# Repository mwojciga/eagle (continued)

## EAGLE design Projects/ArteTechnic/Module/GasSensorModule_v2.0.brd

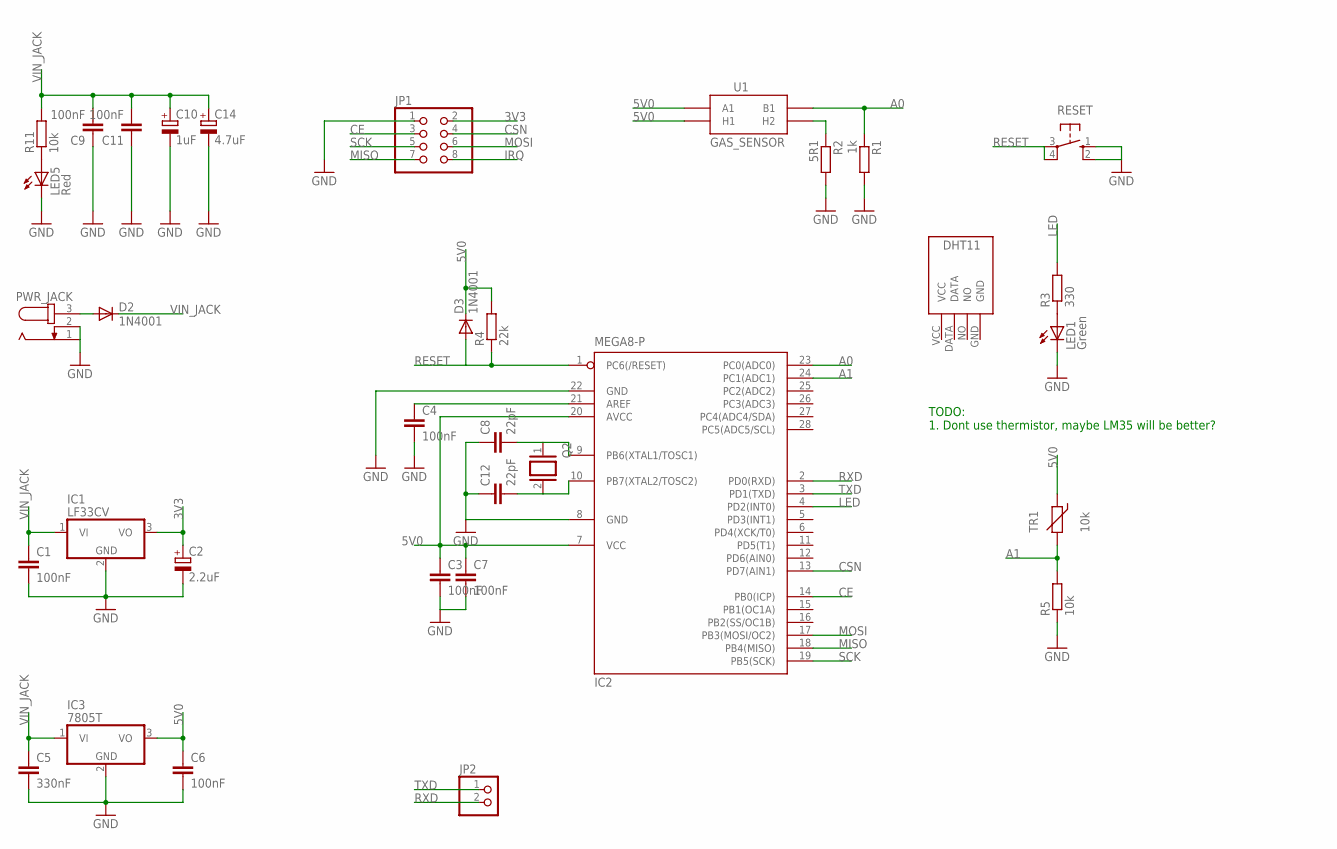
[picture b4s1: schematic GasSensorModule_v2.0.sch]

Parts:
C1, C3, C4, C6, C7, C9, C11: 100nF; C025-025X050
C2: 2.2uF; E2,5-5
C5: 330nF; C025-025X050
C8, C12: 22pF; C025-025X050
C10: 1uF; E2,5-5
C14: 4.7uF; E2,5-5
D2, D3: 1N4001; DO41-10
IC1: LF33CV; TO220H
IC2: MEGA8-P; DIL28-3
IC3: 7805T; TO220H
JP1: PINHD-2X4; 2X04
JP2: PINHD-1X2/90; 1X02/90
LED1: Green; LED3MM
LED5: Red; LED3MM
PWR_JACK: JACK-PLUG0; SPC4077
Q2: XTAL/S; QS
R1: 1k; 0207/10
R2: 5R1; 0207/10
R3: 330; 0207/10
R4: 22k; 0207/10
R5, R11: 10k; 0207/10
RESET: 10-XX; B3F-10XX
TR1: 10k; RS-2,5
U1: GAS_SENSOR; MQ-3
U$1: DHT11-PION.

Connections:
3V3: C2.+, IC1.3 (VO), JP1.2
5V0: C3.1, C6.1, C7.1, D3.C, IC2.7 (VCC), IC2.20 (AVCC), IC3.3 (VO), R4.2, TR1.1, U1.A1, U1.HA (H1)
A0: IC2.23 (PC0(ADC0)), R1.1, U1.B1
A1: IC2.24 (PC1(ADC1)), R5.2, TR1.2
CE: IC2.14 (PB0(ICP)), JP1.3
CSN: IC2.13 (PD7(AIN1)), JP1.4
GND: C1.2, C2.-, C3.2, C4.2, C5.2, C6.2, C7.2, C8.1, C9.1, C10.-, C11.1, C12.1, C14.-, IC1.2 (GND), IC2.8 (GND), IC2.22 (GND), IC3.2 (GND), JP1.1, LED1.K (C), LED5.K (C), PWR_JACK.1, PWR_JACK.2, R1.2, R2.2, R5.1, RESET.1 (S), RESET.2 (S1)
IRQ: JP1.8
LED: IC2.4 (PD2(INT0)), R3.2
MISO: IC2.18 (PB4(MISO)), JP1.7
MOSI: IC2.17 (PB3(MOSI/OC2)), JP1.6
unnamed: C4.1, IC2.21 (AREF)
unnamed: R2.1, U1.HB (H2)
unnamed: D2.A, PWR_JACK.3
unnamed: LED1.A, R3.1
unnamed: LED5.A, R11.1
unnamed: C8.2, IC2.9 (PB6(XTAL1/TOSC1)), Q2.1
unnamed: C12.2, IC2.10 (PB7(XTAL2/TOSC2)), Q2.2
RESET: D3.A, IC2.1 (PC6(/RESET)), R4.1, RESET.3, RESET.4 (P1)
RXD: IC2.2 (PD0(RXD)), JP2.2
SCK: IC2.19 (PB5(SCK)), JP1.5
TXD: IC2.3 (PD1(TXD)), JP2.1
VIN_JACK: C1.1, C5.1, C9.2, C10.+, C11.2, C14.+, D2.C, IC1.1 (VI), IC3.1 (VI), R11.2

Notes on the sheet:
TODO: 1. Dont use thermistor, maybe LM35 will be better?

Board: 2 copper layers, 34 parts (0 on the bottom side), 22 nets, no tracks yet.

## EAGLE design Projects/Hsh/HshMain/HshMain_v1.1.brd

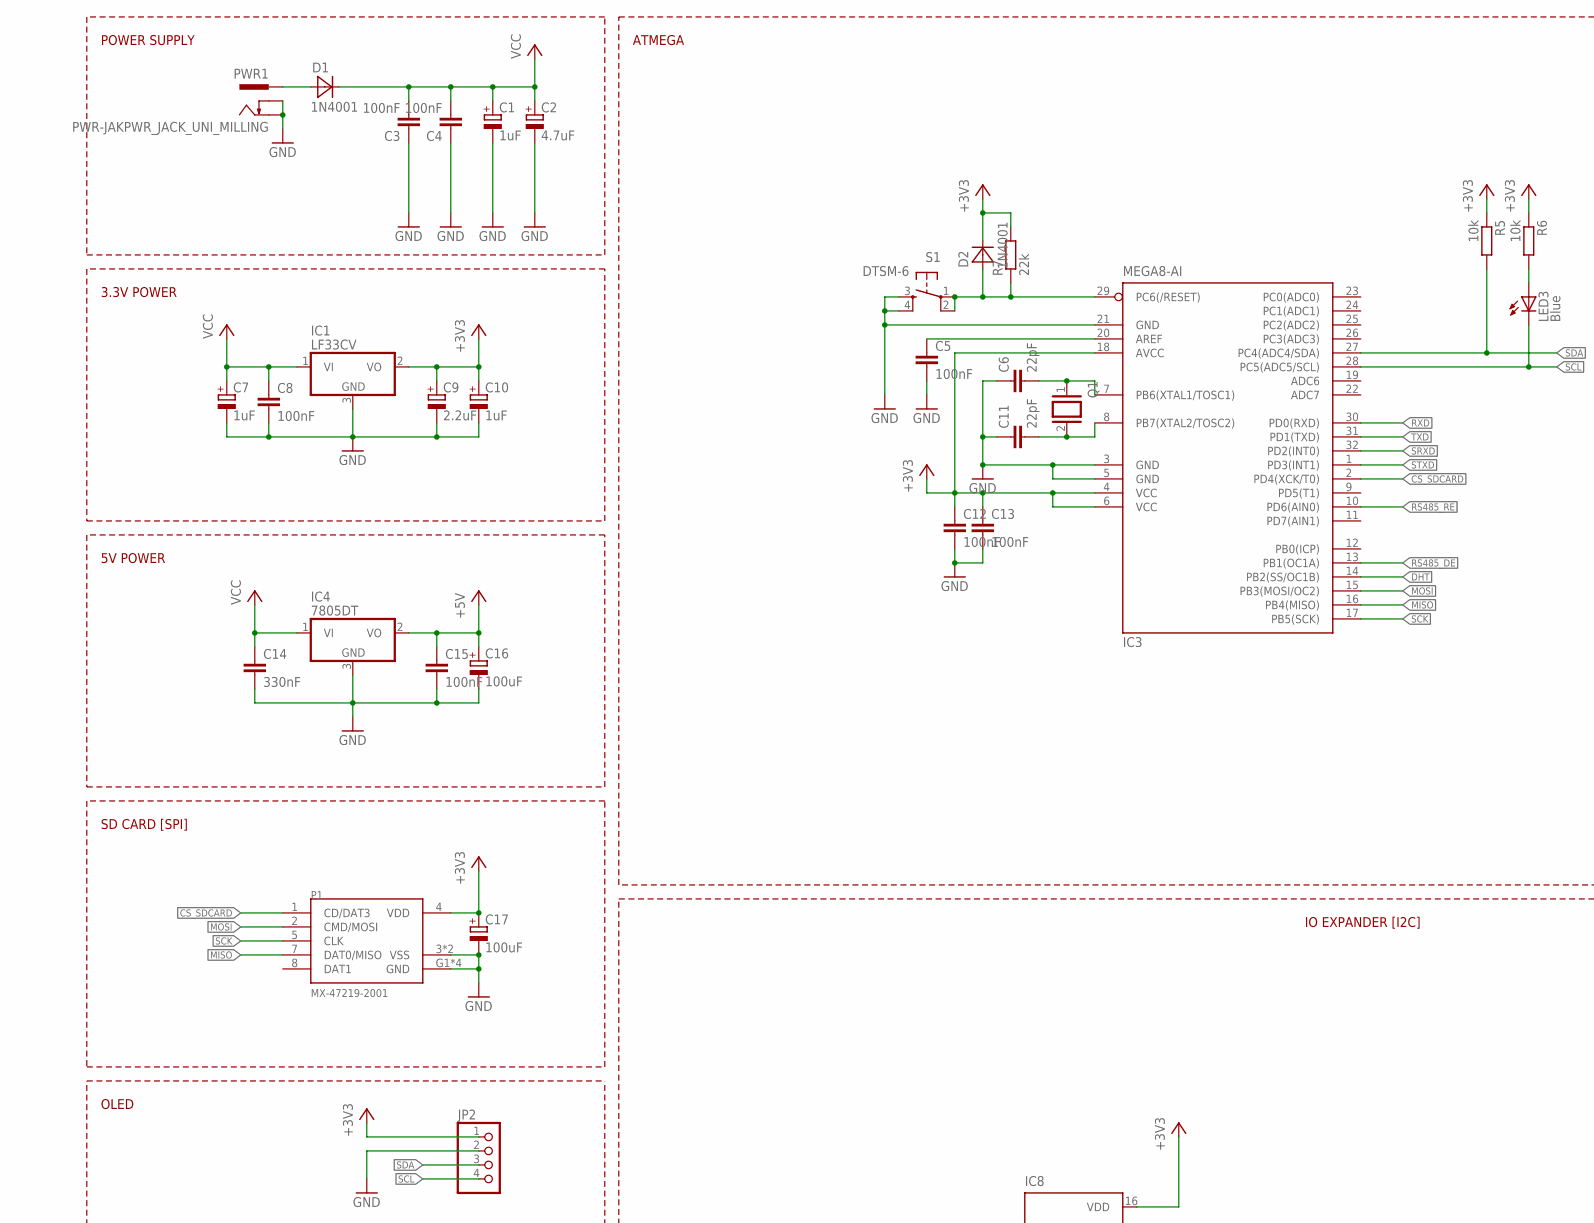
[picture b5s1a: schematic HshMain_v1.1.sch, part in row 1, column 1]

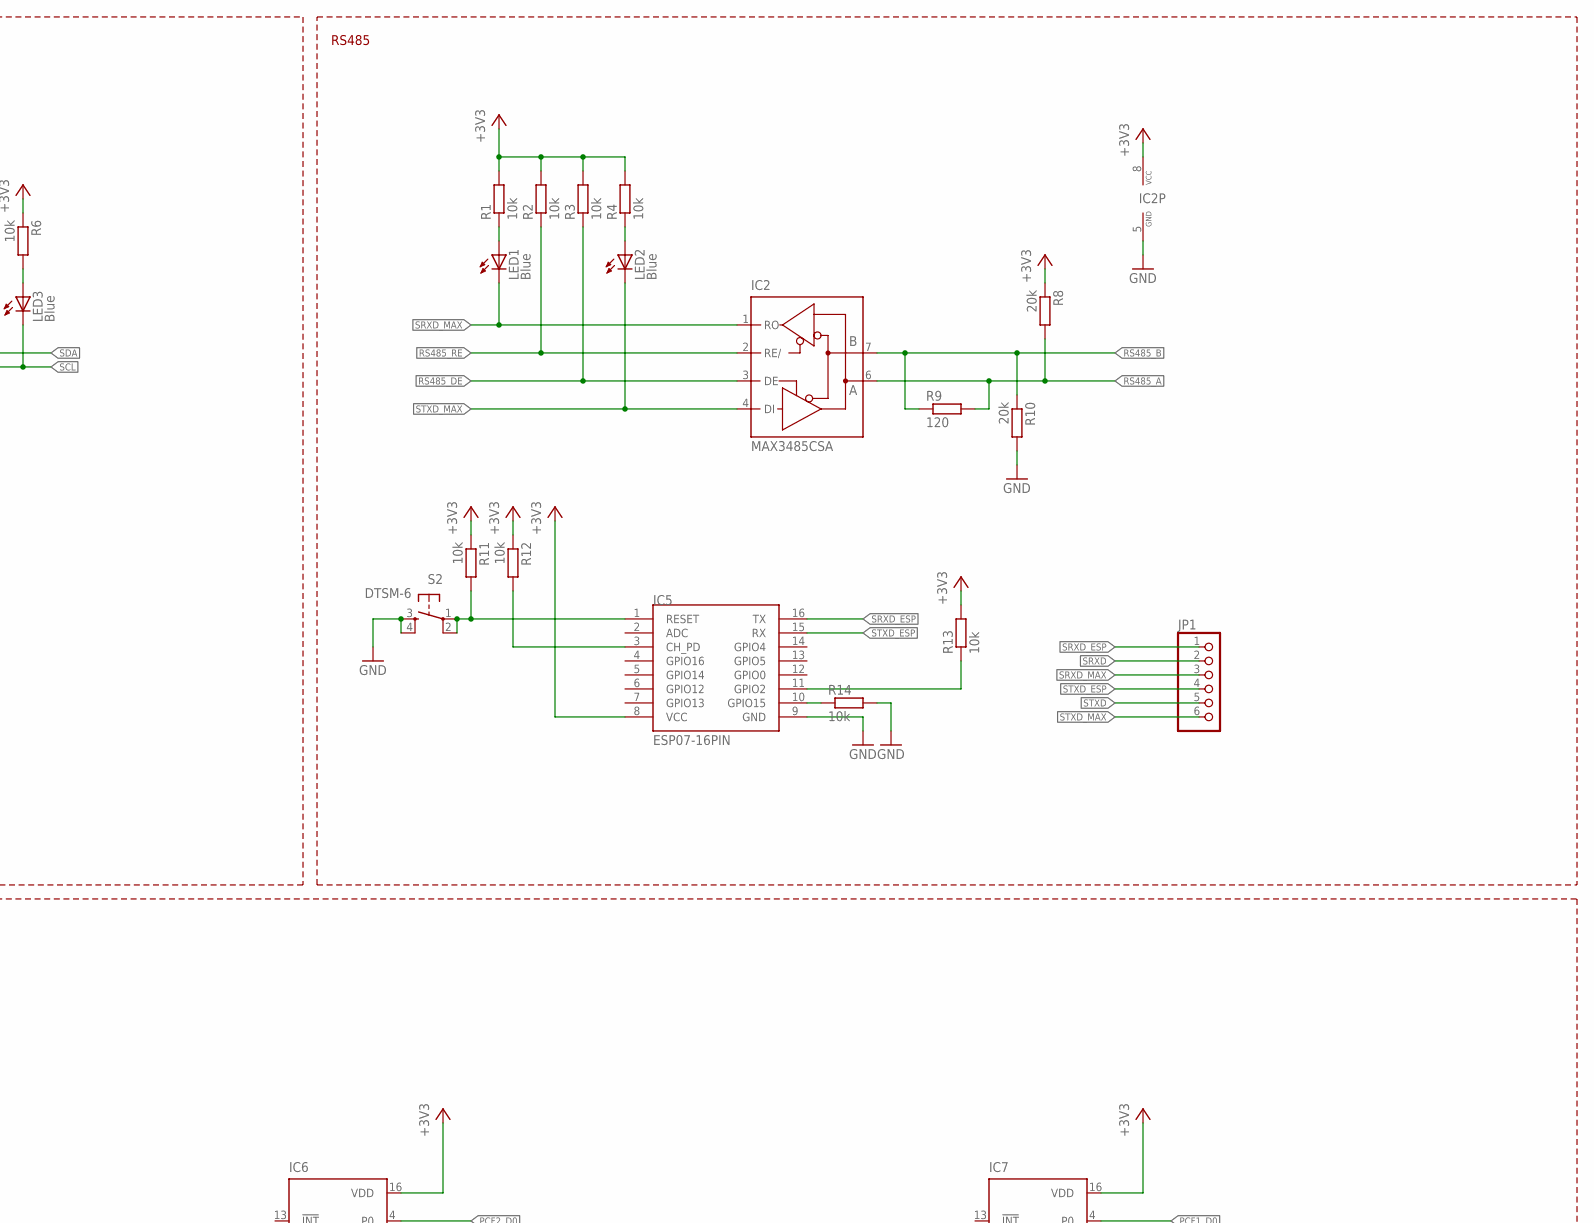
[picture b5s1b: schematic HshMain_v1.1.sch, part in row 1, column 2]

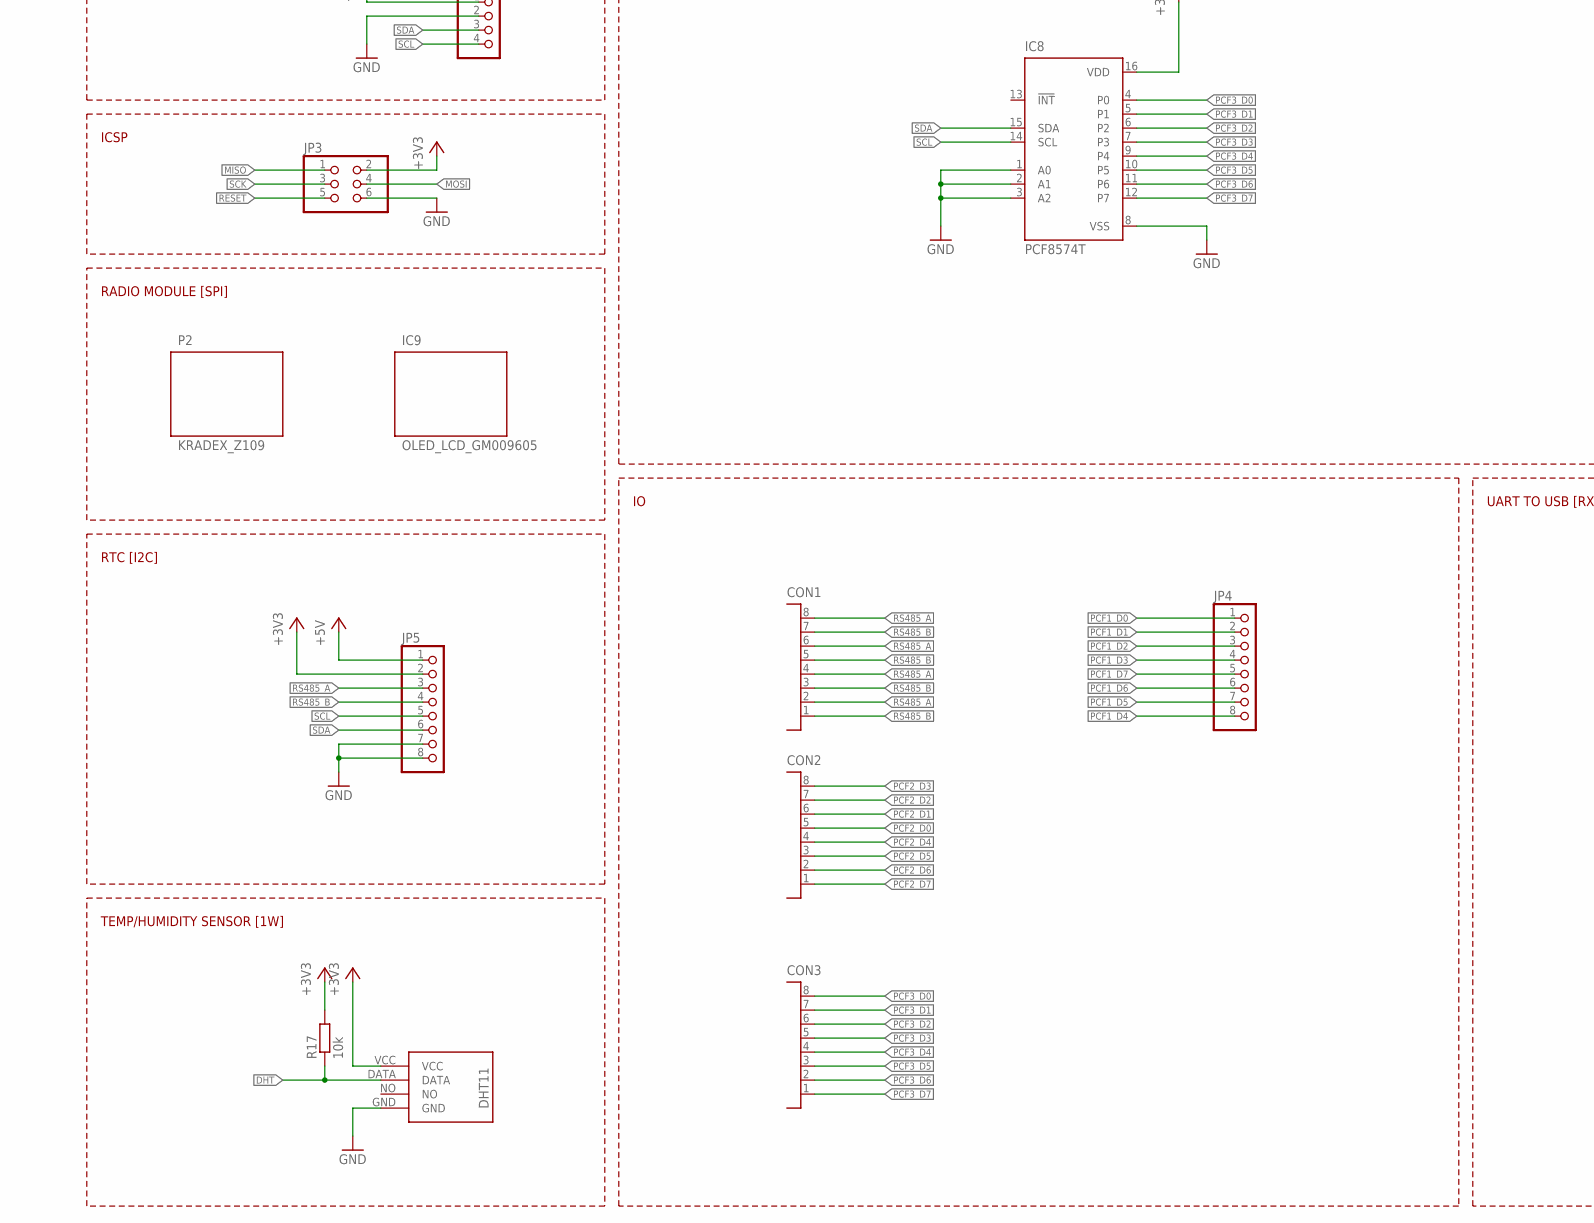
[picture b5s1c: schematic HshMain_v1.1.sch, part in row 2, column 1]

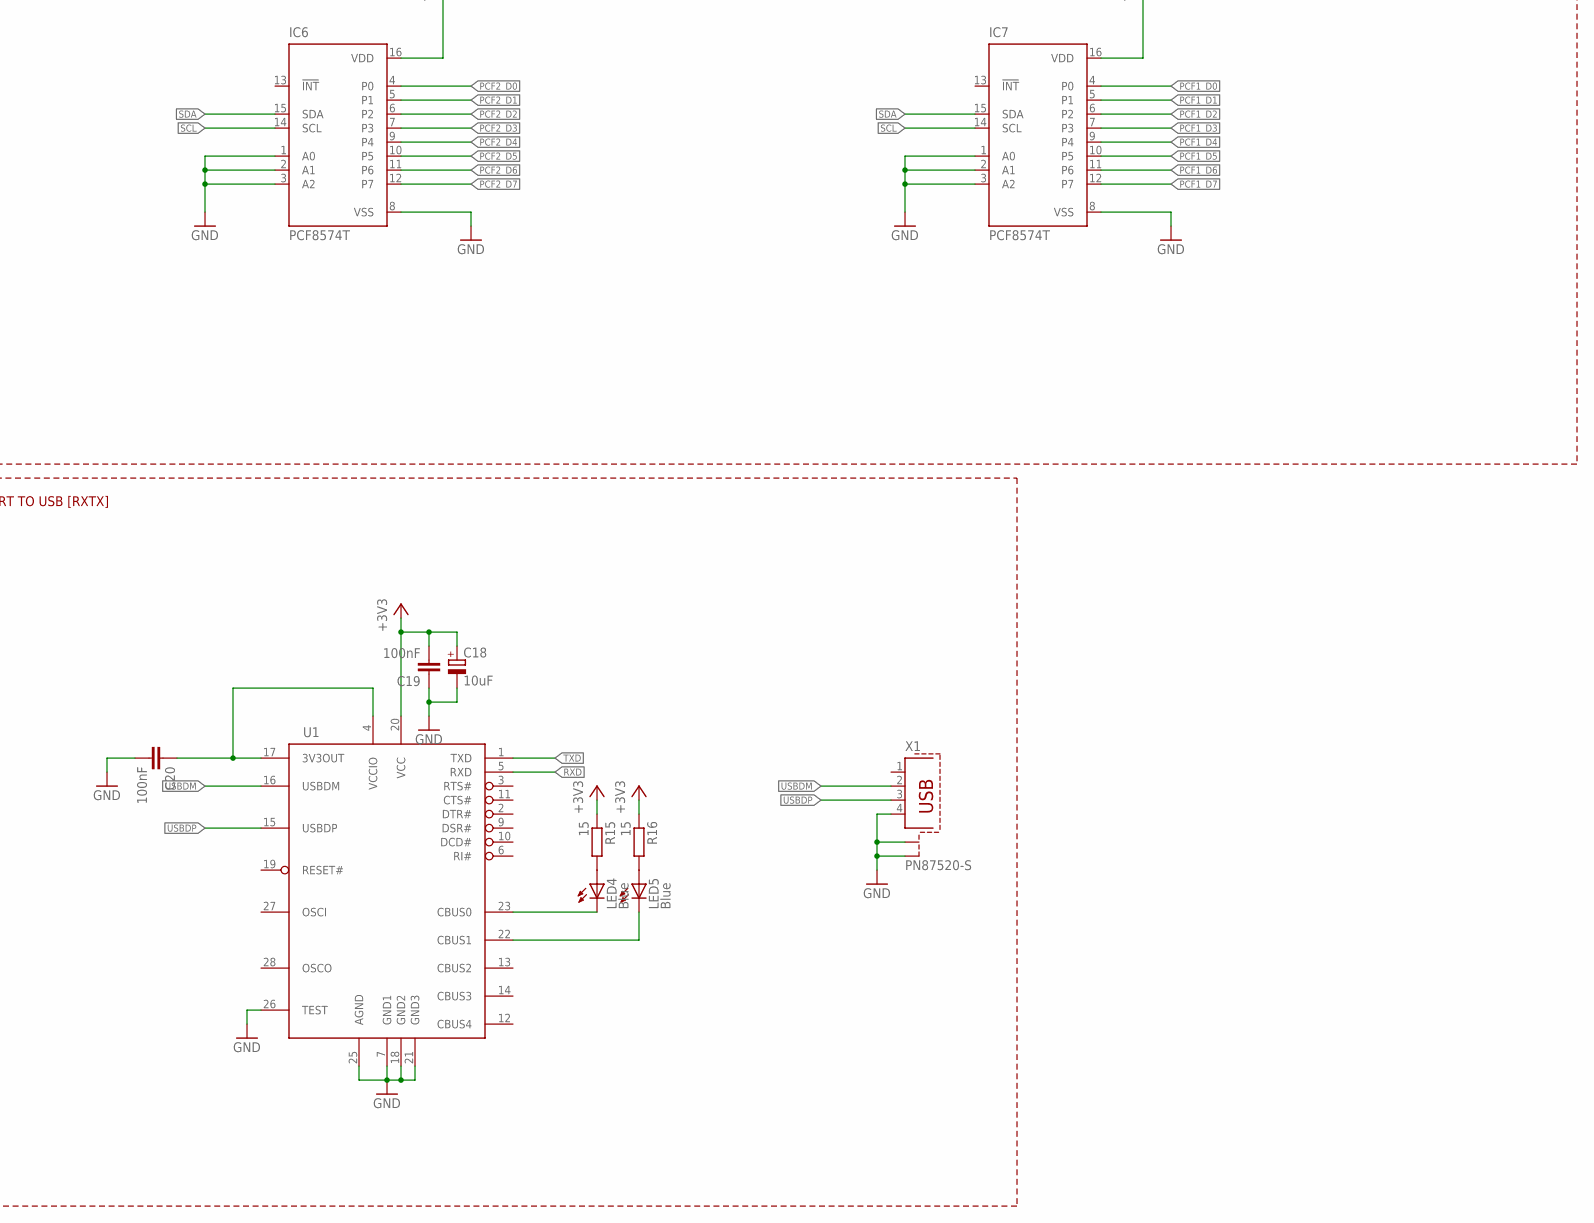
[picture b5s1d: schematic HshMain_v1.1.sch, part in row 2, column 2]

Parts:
C1, C7, C10: 1uF; PANASONIC_B
C2: 4.7uF; PANASONIC_B
C3, C4, C5, C8, C12, C13, C15, C19, C20: 100nF; C0805
C6, C11: 22pF; C0805
C9: 2.2uF; PANASONIC_B
C14: 330nF; C0805
C16, C17: 100uF; PANASONIC_D
C18: 10uF; PANASONIC_B
CON1, CON2, CON3: 15EDGRC-3.81-8P
D1, D2: 1N4001; SMA
IC1: LF33CV; TO252
IC2: MAX3485CSA; SO08
IC3: MEGA8-AI; TQFP32-08
IC4: 7805DT; TO252
IC5: ESP07-16PIN
IC6, IC7, IC8: PCF8574T; SO16W
IC9: OLED_LCD_GM009605
IC10: DHT11-PION.
JP1: PINHD-1X6; 1X06
JP2: PINHD-1X4; 1X04
JP3: PINHD-2X3; 2X03
JP4: PINHD-1X8; 1X08
JP5: PINHD-1X8/90; 1X08/90
LED1, LED2, LED3, LED4, LED5: Blue; SML0805
P1: MX-47219-2001
P2: KRADEX_Z109
PWR1: PWR-JAKPWR_JACK_UNI_MILLING; PWR_JACK_UNI_MILLING
Q1: XTAL/S; QS
R1, R2, R3, R4, R5, R6, R11, R12, R13, R14, R17: 10k; R0805
R7: 22k; R0805
R8, R10: 20k; R0805
R9: 120; R0805
R15, R16: 15; R0805
S1, S2: DTSM-6
U1: FT232RL; SSOP28DB
X1: PN87520-S

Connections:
+3V3: C9.+, C10.+, C12.1, C13.1, C17.+, C18.+, C19.2, D2.C, IC1.2 (VO), IC2.8 (VCC), IC3.4 (VCC), IC3.6 (VCC), IC3.18 (AVCC), IC5.8 (VCC), IC6.16 (VDD), IC7.16 (VDD), IC8.16 (VDD), IC10.VCC, JP2.1, JP3.2, JP5.2, P1.4 (VDD), R1.2, R2.2, R3.2, R4.2, R5.1, R6.1, R7.2, R8.1, R11.1, R12.1, R13.2, R15.1, R16.1, R17.2, U1.20 (VCC)
+5V: C15.1, C16.+, IC4.2 (VO), JP5.1
CS_SDCARD: IC3.2 (PD4(XCK/T0)), P1.1 (CD/DAT3)
DHT: IC3.14 (PB2(SS/OC1B)), IC10.DATA, R17.1
GND: C1.-, C2.-, C3.1, C4.1, C5.2, C6.1, C7.-, C8.2, C9.-, C10.-, C11.1, C12.2, C13.2, C14.2, C15.2, C16.-, C17.-, C18.-, C19.1, C20.2, IC1.3 (GND), IC2.5 (GND), IC3.3 (GND), IC3.5 (GND), IC3.21 (GND), IC4.3 (GND), IC5.9 (GND), IC6.1 (A0), IC6.2 (A1), IC6.3 (A2), IC6.8 (VSS), IC7.1 (A0), IC7.2 (A1), IC7.3 (A2), IC7.8 (VSS), IC8.1 (A0), IC8.2 (A1), IC8.3 (A2), IC8.8 (VSS), IC10.GND, JP2.2, JP3.6, JP5.7, JP5.8, P1.3 (VSS), P1.6 (VSS), P1.G1 (GND), P1.G2 (GND), P1.G3 (GND), P1.G4 (GND), PWR1.-, PWR1.-1 (-), PWR1.-2 (-), PWR1.-3 (-), PWR1.-4 (-), PWR1.-5 (-), PWR1.-6 (-), PWR1.-7 (-), PWR1.-8 (-), PWR1.--, PWR1.--1 (--), PWR1.--2 (--), PWR1.--3 (--), PWR1.--4 (--), PWR1.--5 (--), PWR1.--6 (--), PWR1.--7 (--), PWR1.--8 (--), R10.2, R14.2, S1.3, S1.4, S2.3, S2.4, U1.7 (GND1), U1.18 (GND2), U1.21 (GND3), U1.25 (AGND), U1.26 (TEST), X1.4, X1.S1, X1.S2
MISO: IC3.16 (PB4(MISO)), JP3.1, P1.7 (DAT0/MISO)
MOSI: IC3.15 (PB3(MOSI/OC2)), JP3.4, P1.2 (CMD/MOSI)
unnamed: C5.1, IC3.20 (AREF)
unnamed: LED1.A, R1.1
unnamed: LED2.A, R4.1
unnamed: D1.A, PWR1.+, PWR1.+1 (+), PWR1.+2 (+), PWR1.+3 (+), PWR1.+4 (+), PWR1.+5 (+), PWR1.+6 (+), PWR1.+7 (+), PWR1.+8 (+)
unnamed: LED3.A, R6.2
unnamed: IC5.10 (GPIO15), R14.1
unnamed: IC5.11 (GPIO2), R13.1
unnamed: IC5.1 (RESET), R11.2, S2.1, S2.2
unnamed: IC5.3 (CH_PD), R12.2
unnamed: LED4.C, U1.23 (CBUS0)
unnamed: LED5.C, U1.22 (CBUS1)
unnamed: C6.2, IC3.7 (PB6(XTAL1/TOSC1)), Q1.1
unnamed: LED4.A, R15.2
unnamed: LED5.A, R16.2
unnamed: C11.2, IC3.8 (PB7(XTAL2/TOSC2)), Q1.2
unnamed: C20.1, U1.4 (VCCIO), U1.17 (3V3OUT)
PCF1_D0: IC7.4 (P0), JP4.1
PCF1_D1: IC7.5 (P1), JP4.2
PCF1_D2: IC7.6 (P2), JP4.3
PCF1_D3: IC7.7 (P3), JP4.4
PCF1_D4: IC7.9 (P4), JP4.8
PCF1_D5: IC7.10 (P5), JP4.7
PCF1_D6: IC7.11 (P6), JP4.6
PCF1_D7: IC7.12 (P7), JP4.5
PCF2_D0: CON2.5, IC6.4 (P0)
PCF2_D1: CON2.6, IC6.5 (P1)
PCF2_D2: CON2.7, IC6.6 (P2)
PCF2_D3: CON2.8, IC6.7 (P3)
PCF2_D4: CON2.4, IC6.9 (P4)
PCF2_D5: CON2.3, IC6.10 (P5)
PCF2_D6: CON2.2, IC6.11 (P6)
PCF2_D7: CON2.1, IC6.12 (P7)
PCF3_D0: CON3.8, IC8.4 (P0)
PCF3_D1: CON3.7, IC8.5 (P1)
PCF3_D2: CON3.6, IC8.6 (P2)
PCF3_D3: CON3.5, IC8.7 (P3)
PCF3_D4: CON3.4, IC8.9 (P4)
PCF3_D5: CON3.3, IC8.10 (P5)
PCF3_D6: CON3.2, IC8.11 (P6)
PCF3_D7: CON3.1, IC8.12 (P7)
RESET: D2.A, IC3.29 (PC6(/RESET)), JP3.5, R7.1, S1.1, S1.2
RS485_A: CON1.2, CON1.4, CON1.6, CON1.8, IC2.6 (A), JP5.3, R8.2, R9.2
RS485_B: CON1.1, CON1.3, CON1.5, CON1.7, IC2.7 (B), JP5.4, R9.1, R10.1
RS485_DE: IC2.3 (DE), IC3.13 (PB1(OC1A)), R3.1
RS485_RE: IC2.2 (RE/), IC3.10 (PD6(AIN0)), R2.1
RXD: IC3.30 (PD0(RXD)), U1.5 (RXD)
SCK: IC3.17 (PB5(SCK)), JP3.3, P1.5 (CLK)
SCL: IC3.28 (PC5(ADC5/SCL)), IC6.14 (SCL), IC7.14 (SCL), IC8.14 (SCL), JP2.4, JP5.5, LED3.C
SDA: IC3.27 (PC4(ADC4/SDA)), IC6.15 (SDA), IC7.15 (SDA), IC8.15 (SDA), JP2.3, JP5.6, R5.2
SRXD: IC3.32 (PD2(INT0)), JP1.2
SRXD_ESP: IC5.16 (TX), JP1.1
SRXD_MAX: IC2.1 (RO), JP1.3, LED1.C
STXD: IC3.1 (PD3(INT1)), JP1.5
STXD_ESP: IC5.15 (RX), JP1.4
STXD_MAX: IC2.4 (DI), JP1.6, LED2.C
TXD: IC3.31 (PD1(TXD)), U1.1 (TXD)
USBDM: U1.16 (USBDM), X1.2
USBDP: U1.15 (USBDP), X1.3
VCC: C1.+, C2.+, C3.2, C4.2, C7.+, C8.1, C14.1, D1.C, IC1.1 (VI), IC4.1 (VI)

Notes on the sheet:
POWER SUPPLY
3.3V POWER
ICSP
RADIO MODULE [SPI]
ATMEGA
SD CARD [SPI]
RTC [I2C]
IO EXPANDER [I2C]
TEMP/HUMIDITY SENSOR [1W]
UART TO USB [RXTX]
5V POWER
RS485
OLED

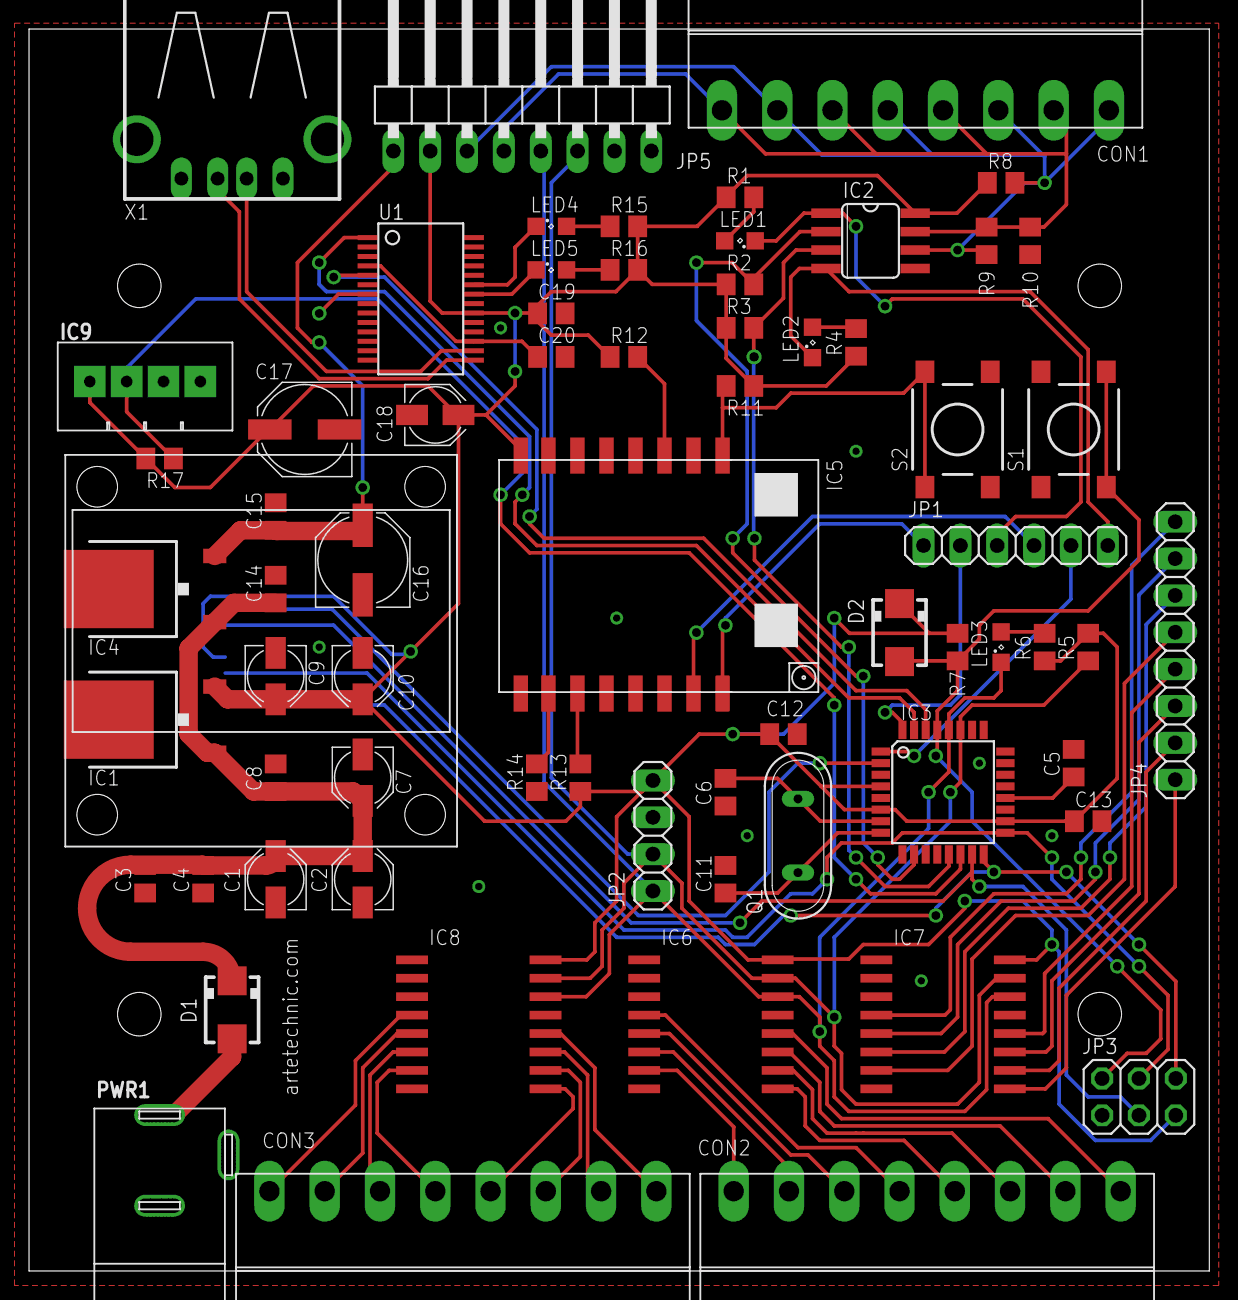
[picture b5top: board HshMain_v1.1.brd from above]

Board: 2 copper layers, 81.3 x 85.6 mm, 70 parts (1 on the bottom side), 66 nets.
